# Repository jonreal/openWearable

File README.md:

# openWearable

A real-time hardware/software platform for wearable robotics development based on the BeagleBone platform.

## Overview

openWearable is an open-source project designed to provide a complete hardware and software solution for developing wearable robotic systems, with a focus on real-time control. The platform utilizes the TI BeagleBone Black's Programmable Real-time Units (PRUs) to achieve deterministic high-speed control loops alongside a full Linux environment.

Current/past applications include:
- Upper limb soft exosuits
- Powered ankle-foot prostheses
- Haptic feedback systems
- EMG/IMU sensing and processing

## Getting Started

### Hardware Requirements
- BeagleBone Black or BeagleBone AI64 (see arm64 branch)
- Compatible sensors (see hardware directory)
- Actuators (PAMs, motors, etc.)

### Software Dependencies
- Recommended OS: Debian Linux 12.x (Bookworm) or later
- Kernel: 5.10.168-ti-r72
- PRU Code Generation Tools

### Installation

1. Clone the repository:
   ```
   git clone https://github.com/jonreal/openWearable.git
   cd openWearable
   ```

2. Build the library first:
   ```
   cd library && make
   ```

3. Build an application:
   ```
   cd ../apps/template && make
   ```

4. Run the application:
   ```
   ./bin/template
   ```

### Device Tree Setup

The device tree configures BeagleBone hardware resources for openWearable. Follow these steps:

1. Clone the BeagleBoard-DeviceTrees repository:
   ```
   git clone https://github.com/beagleboard/BeagleBoard-DeviceTrees.git ~/BeagleBoard-DeviceTrees
   ```

2. Create a symbolic link to your device tree file:

   For BeagleBone Black:
   ```
   cd device-tree
   ln -s $PWD/am335x-boneblack-openWearable.dts ~/BeagleBoard-DeviceTrees/src/arm/
   ```

   For BeagleBone Blue:
   ```
   cd device-tree
   ln -s $PWD/am335x-boneblue-openWearable.dts ~/BeagleBoard-DeviceTrees/src/arm/
   ```

3. Compile and install the device tree:
   ```
   cd ~/BeagleBoard-DeviceTrees
   make install_arm
   ```

4. The compiled device tree files will be installed to `/boot/dtbs/<kernel>/`
   (e.g., `/boot/dtbs/5.10.168-ti-r72/`)

5. Edit `/boot/uEnv.txt` to enable the overlay:
   ```
   sudo nano /boot/uEnv.txt
   ```
   
   Add or modify the following line:
   ```
   dtb=am335x-boneblack-openWearable.dtb   # For BeagleBone Black
   # OR
   dtb=am335x-boneblue-openWearable.dtb    # For BeagleBone Blue
   ```

6. Reboot the BeagleBone:
   ```
   sudo reboot
   ```

## Network Setup
To connect to the BeagleBone to Wi-Fi, follow these steps:
   ```
   iwctl

    [iwctl]# station wlan0 scan
    [iwctl]# station wlan0 get-networks
    [iwctl]# station wlan0 connect <SSID>

   ```

## Project Structure

- `apps/` - Application examples and templates
  - `template/` - Starting point for new applications
  - Various application examples (see below)
- `library/` - Core libraries
  - `include/` - Header files
  - `src/` - CPU-side source files
  - `pru_src/` - PRU-specific source files
- `device-tree/` - Hardware configuration
- `hardware/` - PCB designs and hardware documentation
- `gui/` - Visualization tools
- `utils/` - Utility programs
- `scripts/` - Helper scripts

## Application Development

Each application consists of these core files:
- `state.h` - Memory structure definitions
- `format.c` - Logging format definitions
- `cpuloop.c` - Application CPU logic
- `uiloop.c` - User interface logic
- `pruloop.c` - PRU-specific logic

To create a new application, copy the template directory:
```
cd apps
cp -r template my_new_app
cd my_new_app
```

### Build Commands
- First build the library: `cd library && make`
- Then build the app: `cd apps/[app-name] && make`

## Recent Enhancements

1. **Build System Reorganization (March 2025)**
   - Implemented libowpru.a for sharing PRU driver code
   - Each app links against this shared library
   
2. **DMA for Data Transfer (March 2025)**
   - Added DMA support for logging with performance monitoring
   - Use `-d` flag to disable DMA for benchmarking

3. **Binary Logging (In Progress)**
   - Converting text-based logs to binary format
   - Improving performance by reducing formatting overhead

## Example Applications

- **pamtest**: Test pneumatic artificial muscles (PAMs)
- **haptic-tracking**: Haptic feedback control system
- **buttontest**: Simple I/O demonstration
- **imutest**: Test IMU sensors and data processing
- **reflex**: Demonstrate reflex control algorithms

## Publications Using openWearable

### Soft Wearable Robots for Pediatric Movement Disorders
- Realmuto J, Sanger TD. "Assisting Forearm Function in Children With Movement Disorders via A Soft Wearable Robot With Equilibrium-Point Control." Frontiers in Robotics and AI, 2022; 9:877041. doi:10.3389/frobt.2022.877041.
- Repository branch: [equilibrium-point-study](https://github.com/jonreal/openWearable/tree/equilibrium-point-study)

### Powered Ankle-Foot Prostheses
- Realmuto, J. "Towards Personalized Powered Ankle-Foot Prostheses." Dissertation, 2018.
- Repository branch: [poweredAnkle](https://github.com/jonreal/openWearable/tree/poweredAnkle)

### Haptic Feedback for Lower Limb Prostheses
- Sie A, Realmuto J, Rombokas E. "A Lower Limb Prosthesis Haptic Feedback System for Stair Descent." ASME Design of Medical Devices Conference, 2017. doi:10.1115/DMD2017-3409.
- Repository branch: [hapticFeedback](https://github.com/jonreal/openWearable/tree/hapticFeedback)

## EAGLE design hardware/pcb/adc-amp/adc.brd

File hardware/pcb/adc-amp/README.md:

## ADD Details

This folder contains the schematic and component layout for the ADC amplifier circuit using the ADS131M08IPBS chip. The design was created in Autodesk EAGLE and is intended for precision analog signal acquisition.

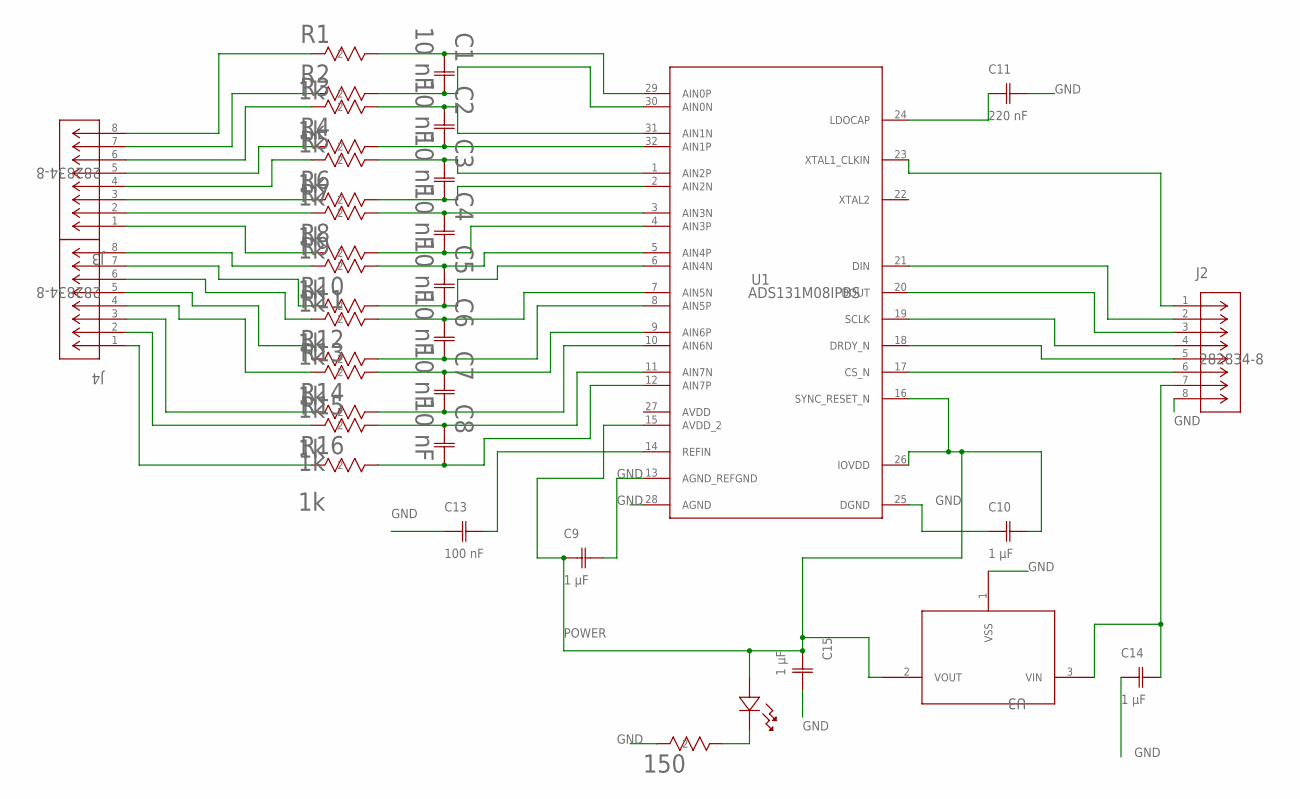
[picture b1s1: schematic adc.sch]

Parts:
C1, C2, C3, C4, C5, C6, C7, C8: 10 nF; CAPC220145_88N_KEM
C9, C10, C14, C15: 1 µF; CAPC220145_140N_KEM
C11: 220 nF; CAPC220145_100N_KEM
C13: 100 nF; CAPC220145_88N_KEM
J2, J3, J4: 282834-8; CONN_282834-8_TEC
LED1: LTST-C190KFKT; LED_LSTS-C190_LTO
R1, R2, R3, R4, R5, R6, R7, R8, R9, R10, R11, R12, R13, R14, R15, R16: 1k; RC0402N_YAG-M
R18: 150; RC0402N_YAG-M
U1: ADS131M08IPBS; PBS0032A_N
U3: XC6206P332MR-GSOT-23_TOR-L; SOT-23_TOR-L

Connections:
AVDD: U1.27 (AVDD)
GND: C9.2, C10.1, C11.2, C13.1, C14.1, C15.2, J2.8, R18.2, U1.13 (AGND_REFGND), U1.25 (DGND), U1.28 (AGND), U3.1 (VSS)
unnamed: C1.1, R1.1, U1.29 (AIN0P)
unnamed: C1.2, R2.1, U1.30 (AIN0N)
unnamed: C2.1, R3.1, U1.31 (AIN1N)
unnamed: C2.2, R4.1, U1.32 (AIN1P)
unnamed: C3.1, R5.1, U1.1 (AIN2P)
unnamed: C3.2, R6.1, U1.2 (AIN2N)
unnamed: C4.1, R7.1, U1.3 (AIN3N)
unnamed: C4.2, R8.1, U1.4 (AIN3P)
unnamed: C5.1, R9.1, U1.5 (AIN4P)
unnamed: C5.2, R10.1, U1.6 (AIN4N)
unnamed: C6.1, R11.1, U1.7 (AIN5N)
unnamed: C6.2, R12.1, U1.8 (AIN5P)
unnamed: C7.1, R13.1, U1.9 (AIN6P)
unnamed: C7.2, R14.1, U1.10 (AIN6N)
unnamed: C8.1, R15.1, U1.11 (AIN7N)
unnamed: C8.2, R16.1, U1.12 (AIN7P)
unnamed: C11.1, U1.24 (LDOCAP)
unnamed: J2.1, U1.23 (XTAL1_CLKIN)
unnamed: J3.8, R1.2
unnamed: J3.7, R2.2
unnamed: J3.6, R3.2
unnamed: J3.5, R4.2
unnamed: J3.4, R5.2
unnamed: J3.3, R6.2
unnamed: J3.2, R7.2
unnamed: J3.1, R8.2
unnamed: J4.8, R9.2
unnamed: J4.7, R10.2
unnamed: J4.6, R11.2
unnamed: J4.5, R12.2
unnamed: J4.4, R13.2
unnamed: J4.3, R14.2
unnamed: J4.2, R15.2
unnamed: J4.1, R16.2
unnamed: J2.4, U1.19 (SCLK)
unnamed: J2.6, U1.17 (CS_N)
unnamed: J2.5, U1.18 (DRDY_N)
unnamed: J2.3, U1.20 (DOUT)
unnamed: J2.2, U1.21 (DIN)
unnamed: C13.2, U1.14 (REFIN)
unnamed: LED1.1 (CATHODE), R18.1
unnamed: C14.2, J2.7, U3.3 (VIN)
POWER: C9.1, C10.2, C15.1, LED1.2 (ANODE), U1.15 (AVDD_2), U1.16 (SYNC_RESET_N), U1.26 (IOVDD), U3.2 (VOUT)

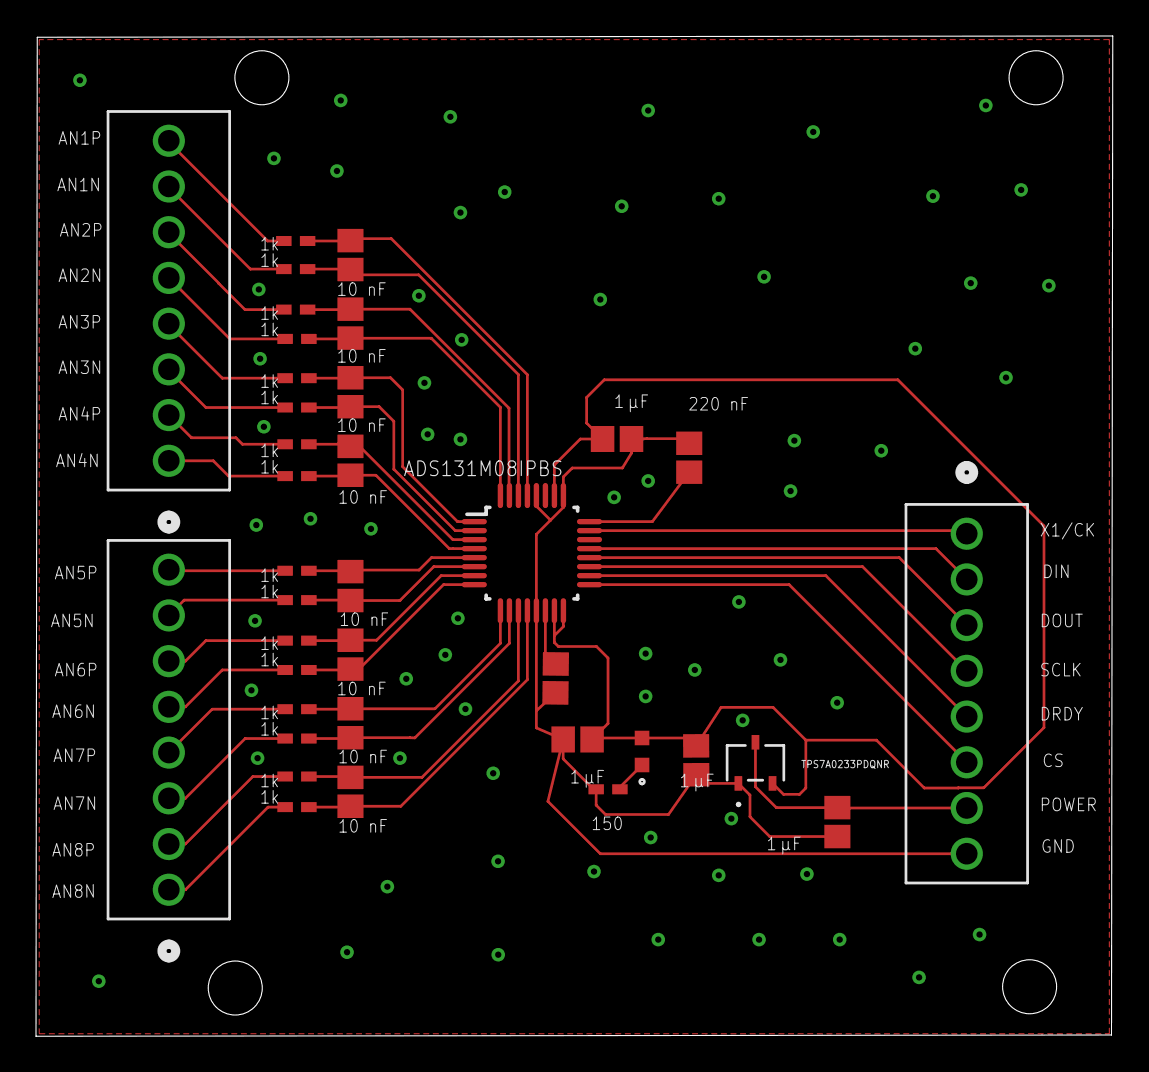
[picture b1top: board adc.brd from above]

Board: 2 copper layers, 59.8 x 55.6 mm, 37 parts (0 on the bottom side), 44 nets.

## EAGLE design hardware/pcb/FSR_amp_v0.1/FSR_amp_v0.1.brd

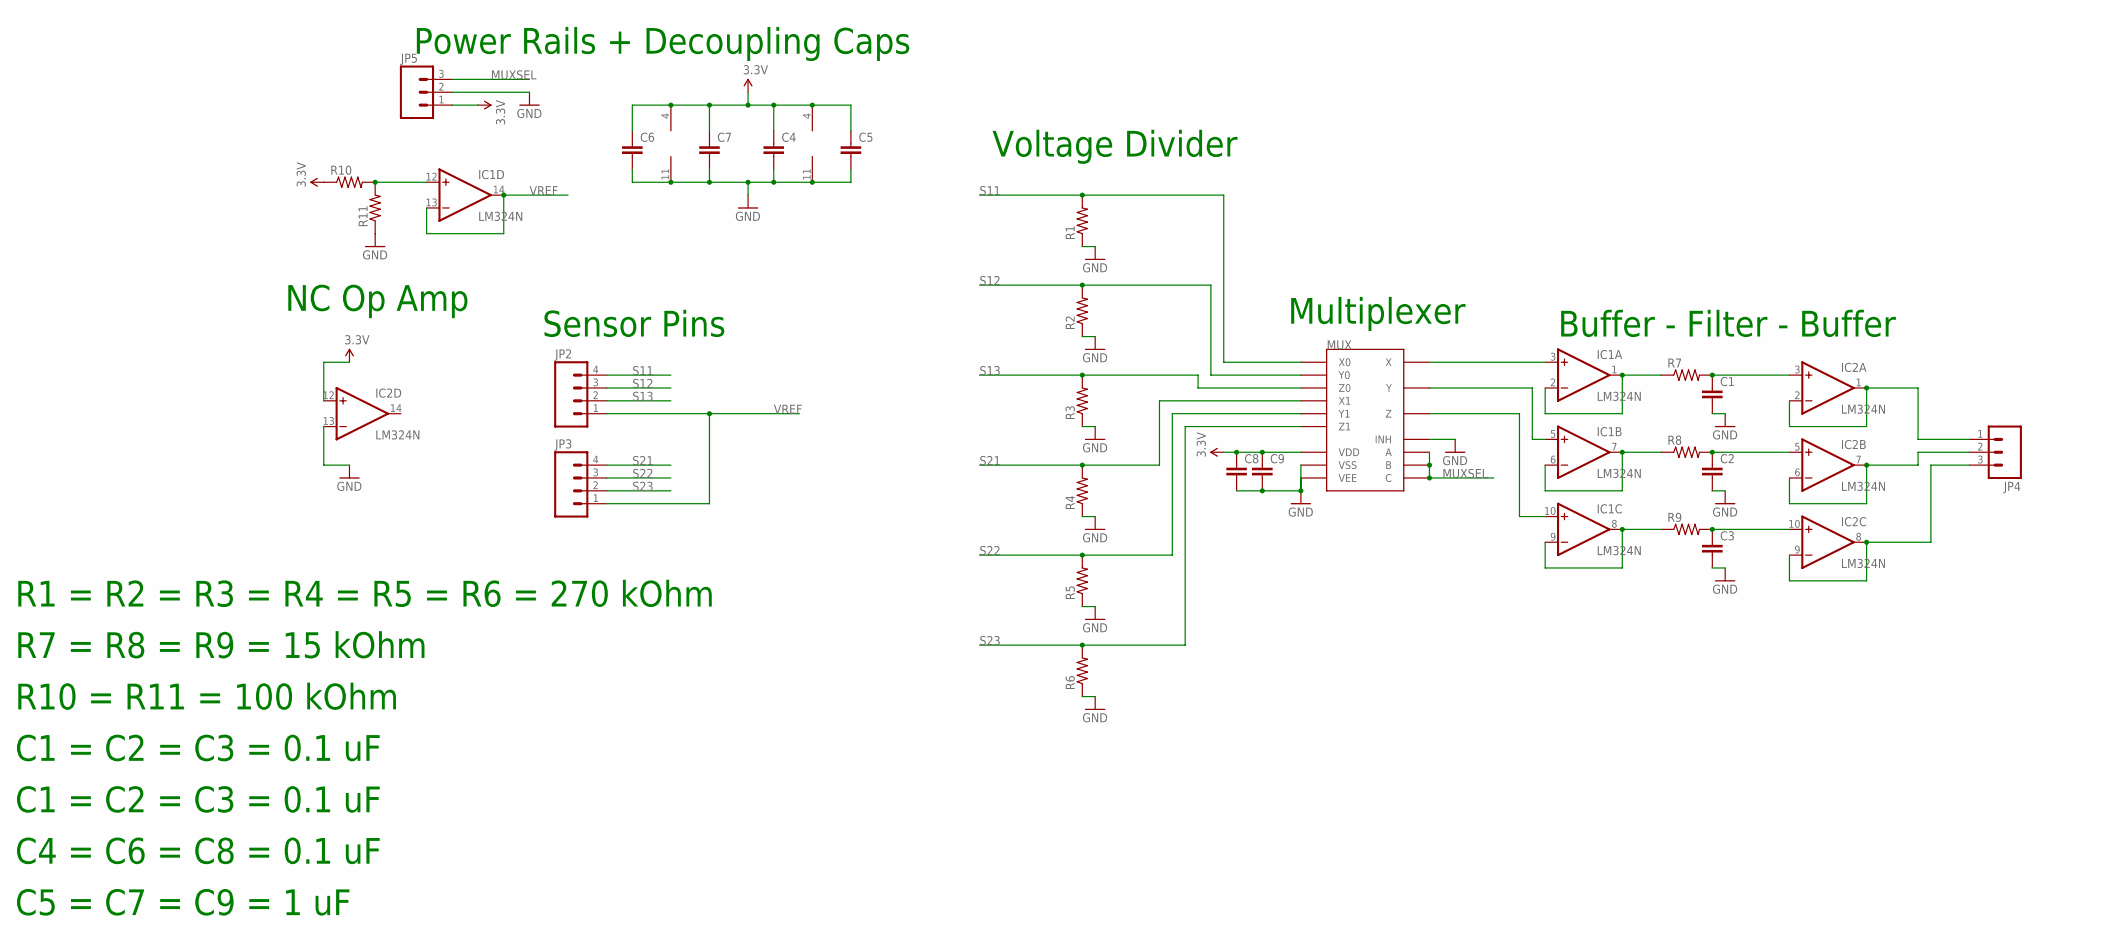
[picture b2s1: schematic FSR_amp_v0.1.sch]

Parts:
C1, C2, C3, C4, C5, C6, C7, C8, C9: CAPPTH; CAP-PTH-SMALL
IC1, IC2: LM324N; DIL14
JP2, JP3: M04POLAR; MOLEX-1X4
JP4, JP5: M03POLAR; MOLEX-1X3
MUX: MC14053BCPDIL16; DIL16
R1, R2, R3, R4, R5, R6, R7, R8, R9, R10, R11: R-US_0207/10; 0207/10

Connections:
3.3V: C4.1, C5.1, C6.1, C7.1, C8.1, C9.1, IC1.4 (V+), IC2.4 (V+), IC2.12 (+IN), JP5.1, MUX.16 (VDD), R10.1
GND: C1.2, C2.2, C3.2, C4.2, C5.2, C6.2, C7.2, C8.2, C9.2, IC1.11 (V-), IC2.11 (V-), IC2.13 (-IN), JP5.2, MUX.6 (INH), MUX.7 (VEE), MUX.8 (VSS), R1.1, R2.1, R3.1, R4.1, R5.1, R6.1, R11.1
MUXSEL: JP5.3, MUX.9 (C), MUX.10 (B), MUX.11 (A)
unnamed: IC1.1 (OUT), IC1.2 (-IN), R7.1
unnamed: IC1.3 (+IN), MUX.14 (X)
unnamed: IC1.6 (-IN), IC1.7 (OUT), R8.1
unnamed: IC1.5 (+IN), MUX.15 (Y)
unnamed: IC1.8 (OUT), IC1.9 (-IN), R9.1
unnamed: IC1.10 (+IN), MUX.4 (Z)
unnamed: IC1.12 (+IN), R10.2, R11.2
unnamed: C1.1, IC2.3 (+IN), R7.2
unnamed: C2.1, IC2.5 (+IN), R8.2
unnamed: C3.1, IC2.10 (+IN), R9.2
unnamed: IC2.8 (OUT), IC2.9 (-IN), JP4.3
unnamed: IC2.6 (-IN), IC2.7 (OUT), JP4.2
unnamed: IC2.1 (OUT), IC2.2 (-IN), JP4.1
S11: JP2.4, MUX.12 (X0), R1.2
S12: JP2.3, MUX.2 (Y0), R2.2
S13: JP2.2, MUX.5 (Z0), R3.2
S21: JP3.4, MUX.13 (X1), R4.2
S22: JP3.3, MUX.1 (Y1), R5.2
S23: JP3.2, MUX.3 (Z1), R6.2
VREF: IC1.13 (-IN), IC1.14 (OUT), JP2.1, JP3.1

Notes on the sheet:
Power Rails + Decoupling Caps
Sensor Pins
Voltage Divider
Multiplexer
Buffer - Filter - Buffer
NC Op Amp
R1 = R2 = R3 = R4 = R5 = R6 = 270 kOhm
R7 = R8 = R9 = 15 kOhm
R10 = R11 = 100 kOhm
C1 = C2 = C3 = 0.1 uF
C4 = C6 = C8 = 0.1 uF
C5 = C7 = C9 = 1 uF

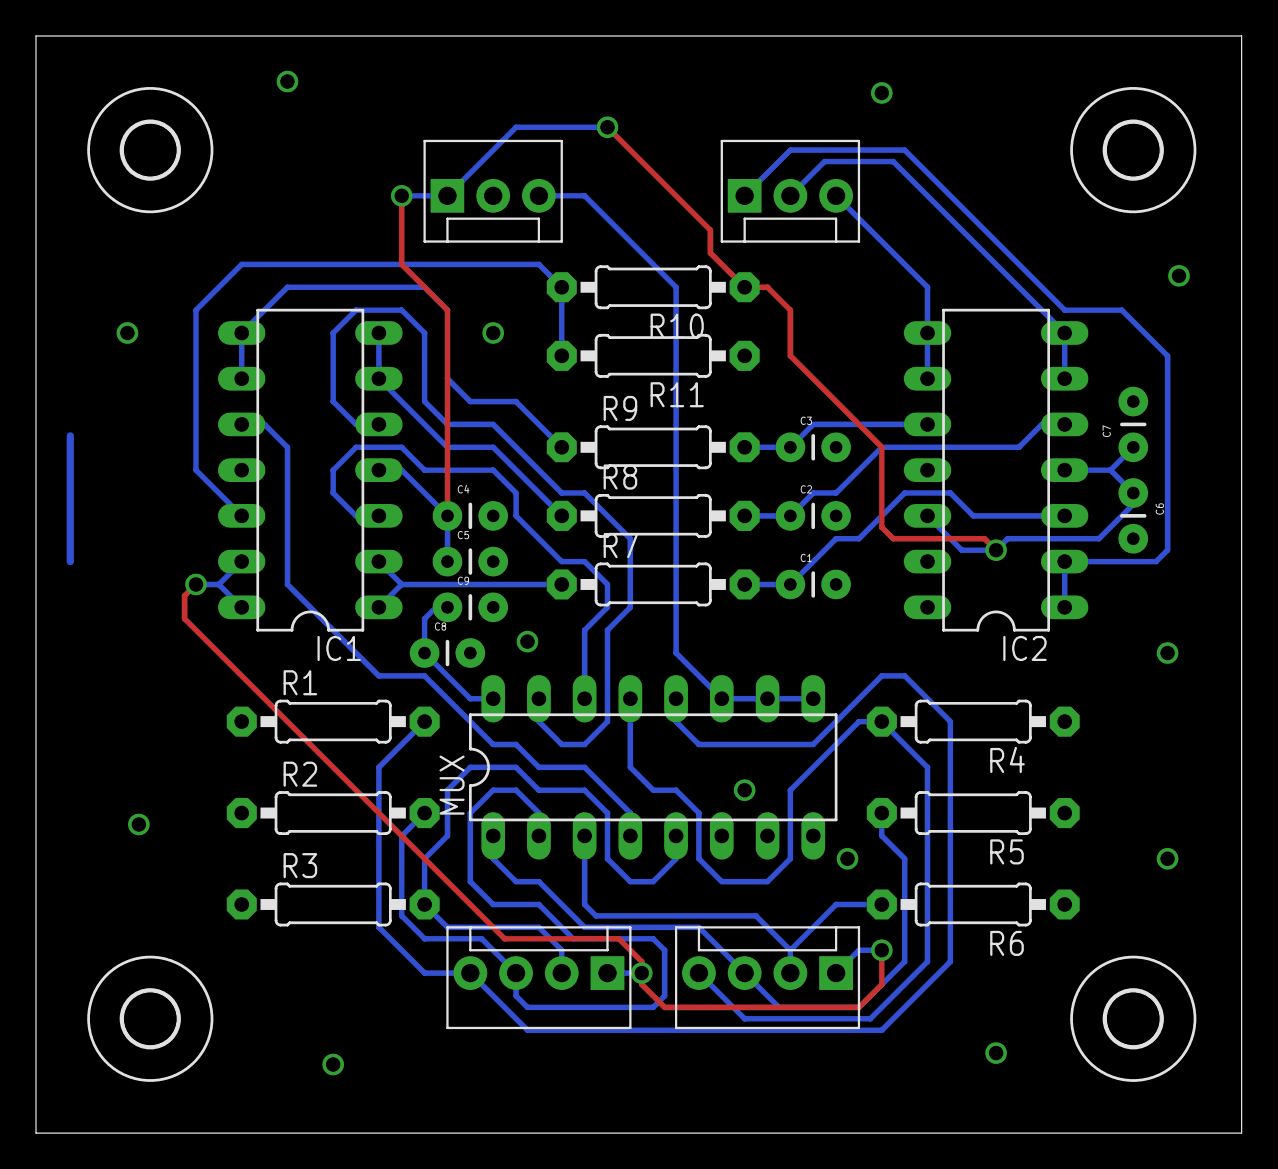
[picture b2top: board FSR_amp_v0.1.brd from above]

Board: 2 copper layers, 67.0 x 61.0 mm, 31 parts (0 on the bottom side), 23 nets.

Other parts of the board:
U$1, U$2, U$3, U$4: 3,0

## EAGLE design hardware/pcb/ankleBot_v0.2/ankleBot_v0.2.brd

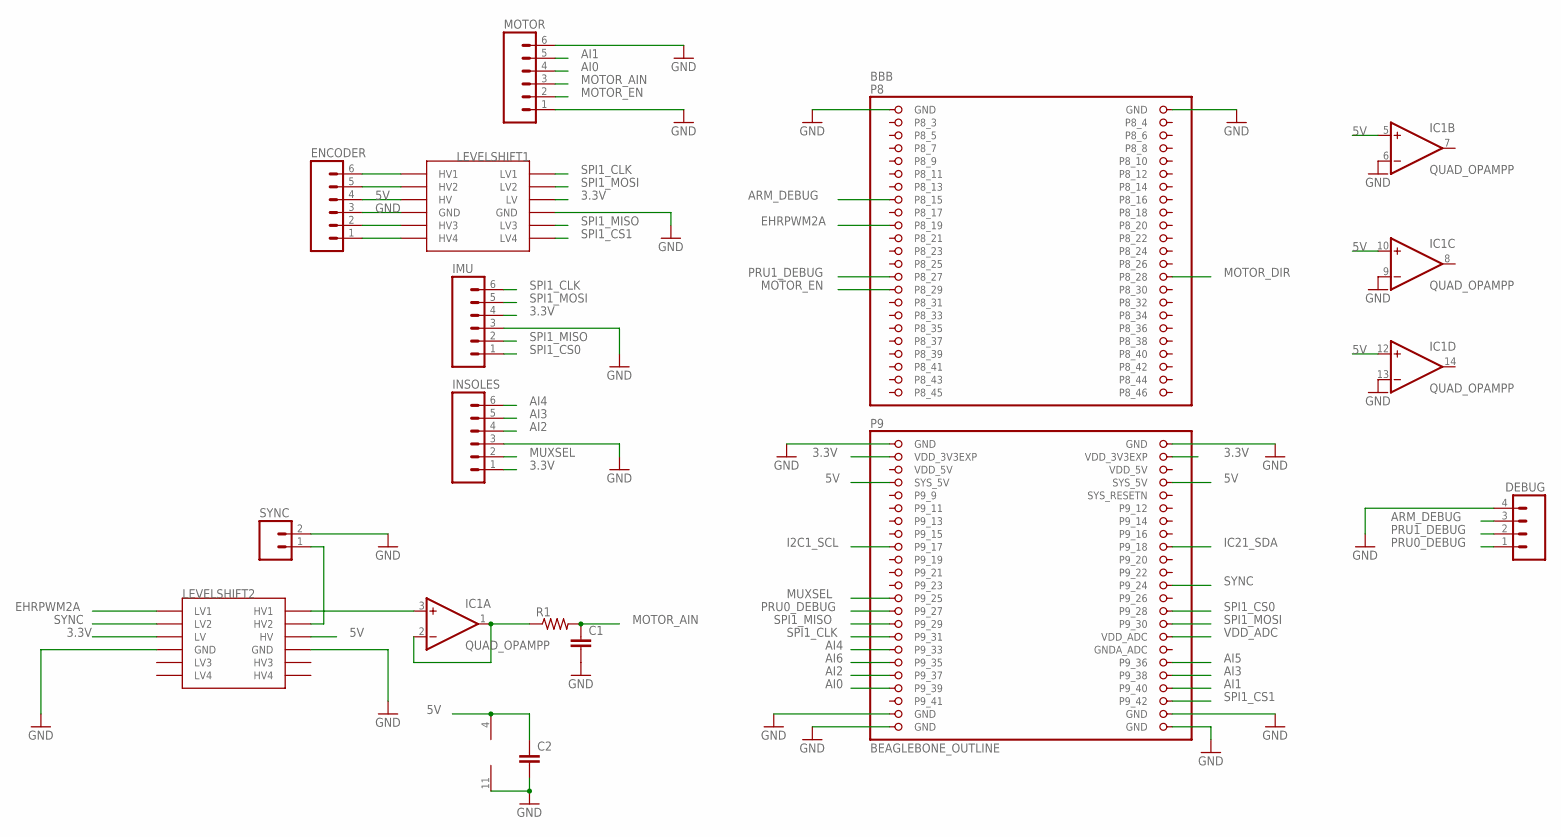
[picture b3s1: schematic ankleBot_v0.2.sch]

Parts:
BBB: BEAGLEBONE_OUTLINE; BEAGLEBONE_SHIELD
C1, C2: C-EU025-025X050; C025-025X050
DEBUG: M04PTH; 1X04
ENCODER: M06POLAR; MOLEX-1X6
IC1: QUAD_OPAMPP; DIL14
IMU: M06POLAR; MOLEX-1X6
INSOLES: M06POLAR; MOLEX-1X6
LEVELSHIFT1, LEVELSHIFT2: SF_LEVEL_CONVERTER; SF_LEVEL_CONVERT
MOTOR: M06POLAR; MOLEX-1X6
R1: R-US_0204/7; 0204/7
SYNC: M02POLAR; MOLEX-1X2

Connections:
3.3V: BBB.49 (VDD_3V3EXP), BBB.50 (VDD_3V3EXP), IMU.4, INSOLES.1, LEVELSHIFT1.P$3 (LV), LEVELSHIFT2.P$3 (LV)
5V: BBB.53 (SYS_5V), BBB.54 (SYS_5V), C2.1, ENCODER.4, IC1.4 (V+), IC1.5 (+IN), IC1.10 (+IN), IC1.12 (+IN), LEVELSHIFT1.P$10 (HV), LEVELSHIFT2.P$10 (HV)
AI0: BBB.85 (P9_39), MOTOR.4
AI1: BBB.86 (P9_40), MOTOR.5
AI2: BBB.83 (P9_37), INSOLES.4
AI3: BBB.84 (P9_38), INSOLES.5
AI4: BBB.79 (P9_33), INSOLES.6
AI5: BBB.82 (P9_36)
AI6: BBB.81 (P9_35)
ARM_DEBUG: BBB.15 (P8_15), DEBUG.3
EHRPWM2A: BBB.19 (P8_19), LEVELSHIFT2.P$1 (LV1)
GND: BBB.1 (GND), BBB.2 (GND), BBB.47 (GND), BBB.48 (GND), BBB.89 (GND), BBB.90 (GND), BBB.91 (GND), BBB.92 (GND), C1.2, C2.2, DEBUG.4, ENCODER.3, IC1.6 (-IN), IC1.9 (-IN), IC1.11 (V-), IC1.13 (-IN), IMU.3, INSOLES.3, LEVELSHIFT1.P$4 (GND), LEVELSHIFT1.P$9 (GND), LEVELSHIFT2.P$4 (GND), LEVELSHIFT2.P$9 (GND), MOTOR.1, MOTOR.6, SYNC.2
I2C1_SCL: BBB.63 (P9_17)
IC21_SDA: BBB.64 (P9_18)
MOTOR_AIN: C1.1, MOTOR.3, R1.2
MOTOR_DIR: BBB.28 (P8_28)
MOTOR_EN: BBB.29 (P8_29), MOTOR.2
MUXSEL: BBB.71 (P9_25), INSOLES.2
unnamed: ENCODER.1, LEVELSHIFT1.P$7 (HV4)
unnamed: IC1.1 (OUT), IC1.2 (-IN), R1.1
unnamed: ENCODER.2, LEVELSHIFT1.P$8 (HV3)
unnamed: LEVELSHIFT2.P$11 (HV2), SYNC.1
unnamed: ENCODER.5, LEVELSHIFT1.P$11 (HV2)
unnamed: ENCODER.6, LEVELSHIFT1.P$12 (HV1)
unnamed: IC1.3 (+IN), LEVELSHIFT2.P$12 (HV1)
PRU0_DEBUG: BBB.73 (P9_27), DEBUG.1
PRU1_DEBUG: BBB.27 (P8_27), DEBUG.2
SPI1_CLK: BBB.77 (P9_31), IMU.6, LEVELSHIFT1.P$1 (LV1)
SPI1_CS0: BBB.74 (P9_28), IMU.1
SPI1_CS1: BBB.88 (P9_42), LEVELSHIFT1.P$6 (LV4)
SPI1_MISO: BBB.75 (P9_29), IMU.2, LEVELSHIFT1.P$5 (LV3)
SPI1_MOSI: BBB.76 (P9_30), IMU.5, LEVELSHIFT1.P$2 (LV2)
SYNC: BBB.70 (P9_24), LEVELSHIFT2.P$2 (LV2)
VDD_5V: BBB.51 (VDD_5V), BBB.52 (VDD_5V)
VDD_ADC: BBB.78 (VDD_ADC)

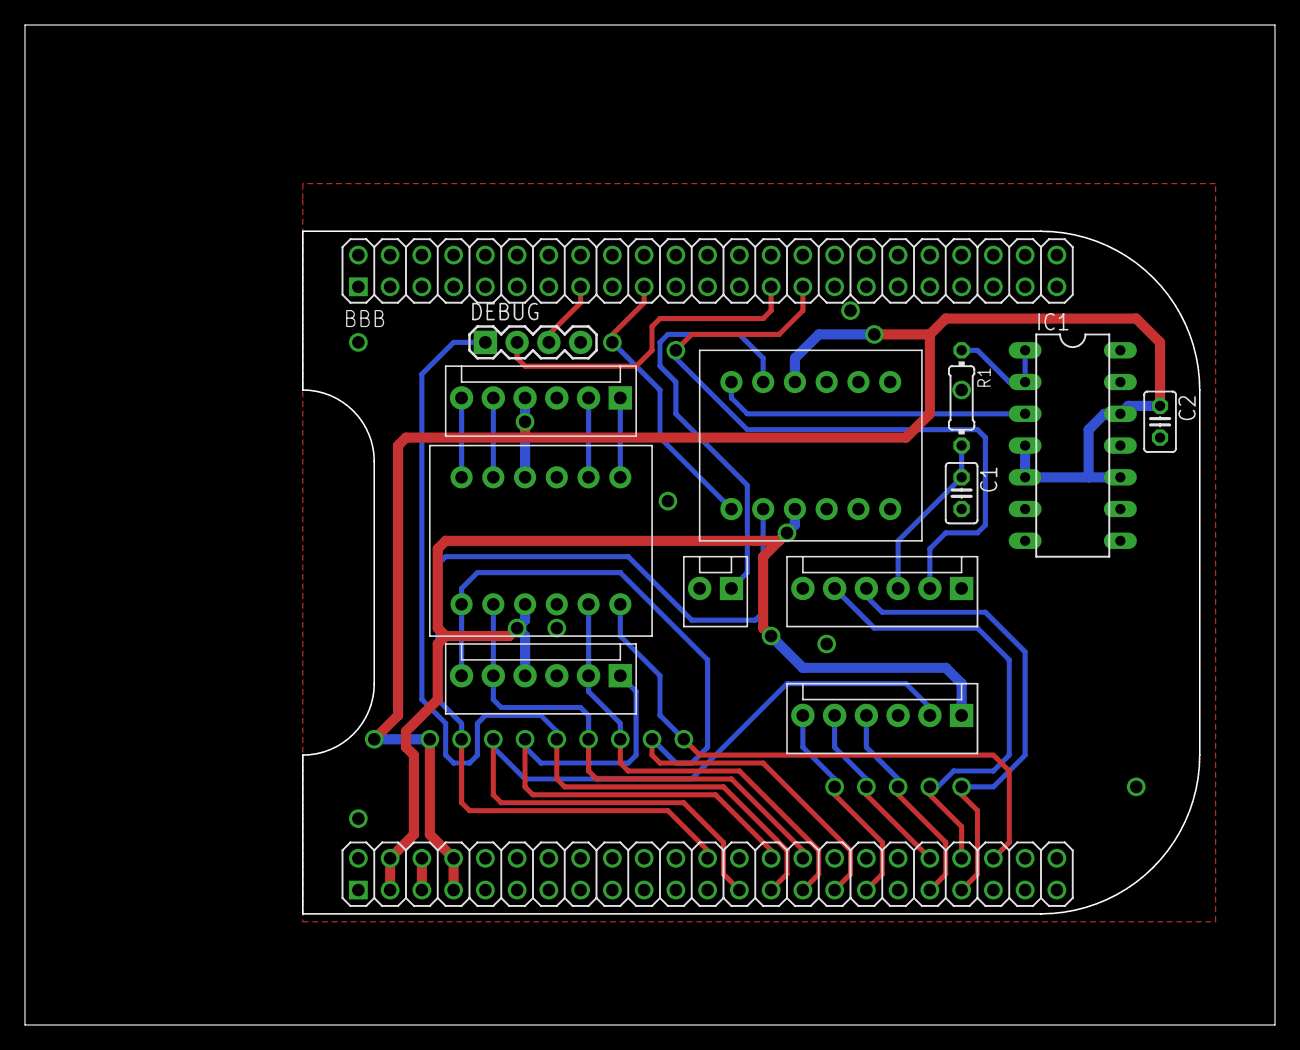
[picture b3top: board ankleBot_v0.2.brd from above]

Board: 2 copper layers, 100.0 x 80.0 mm, 13 parts (0 on the bottom side), 29 nets.

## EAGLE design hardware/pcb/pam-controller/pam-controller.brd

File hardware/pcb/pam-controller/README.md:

This board controls pneumatic valves using a TCA9548A I2C multiplexer and two ULN2803A driver ICs. It supports up to 8 I2C channels and 16 outputs. Logic runs at 3.3V, while VCC supplies power to the valves (e.g., 7V). Use any I2C-capable microcontroller to select channels and drive outputs through the ULN2803A.

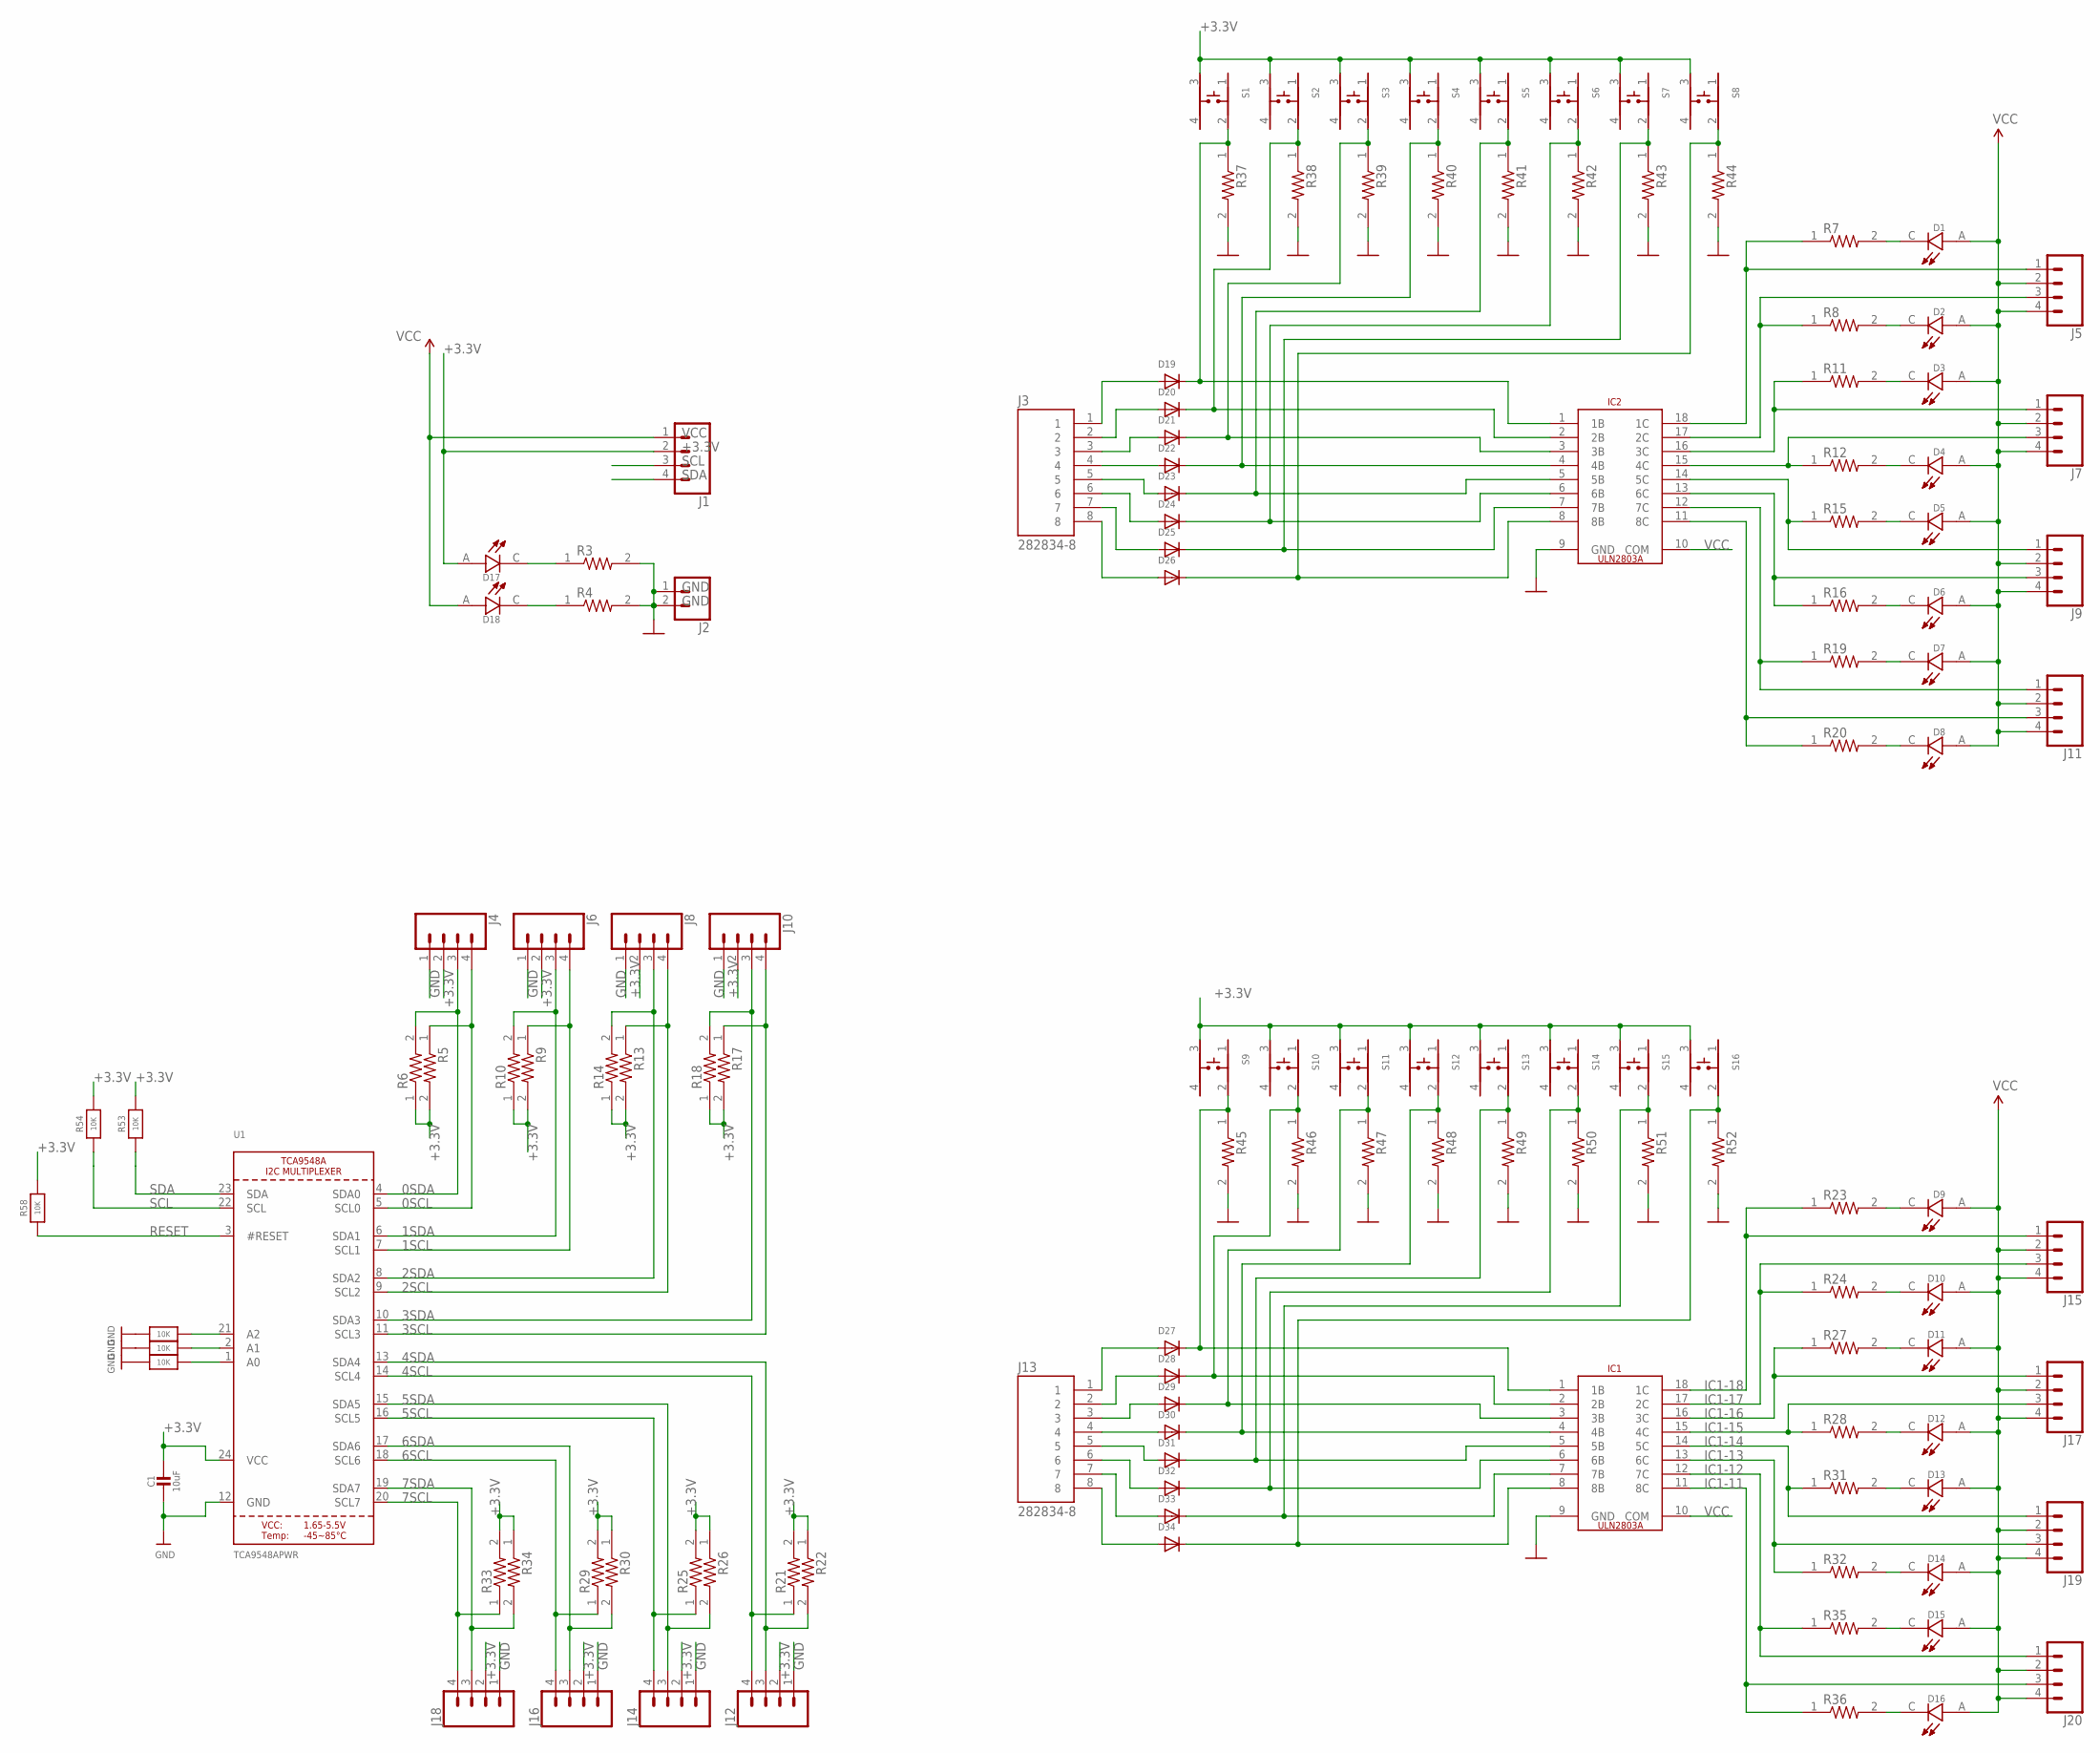
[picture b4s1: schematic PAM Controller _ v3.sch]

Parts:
C1: 10uF; 0805-NO
D1, D2, D3, D4, D5, D6, D7, D8, D9, D10, D11, D12, D13, D14, D15, D16, D17, D18: LTST-C190KGKT; LEDC1608X35N
D19, D20, D21, D22, D23, D24, D25, D26, D27, D28, D29, D30, D31, D32, D33, D34: DIODESOD-523; SOD-523
IC1, IC2: ULN2803A
J1, J4, J5, J6, J7, J8, J9, J10, J11, J12, J14, J15, J16, J17, J18, J19, J20: CONN_04POLAR; MOLEX-1X4
J2: CONN_02POLAR; MOLEX-1X2
J3, J13: 282834-8; TE_282834-8
R3, R4, R5, R6, R7, R8, R9, R10, R11, R12, R13, R14, R15, R16, R17, R18, R19, R20, R21, R22, R23, R24, R25, R26, R27, R28, R29, R30, R31, R32, R33, R34, R35, R36, R37, R38, R39, R40, R41, R42, R43, R44, R45, R46, R47, R48, R49, R50, R51, R52: 1K; RESC1607X60N
R53, R54, R55, R56, R57, R58: 10K; 0805-NO
S1, S2, S3, S4, S5, S6, S7, S8, S9, S10, S11, S12, S13, S14, S15, S16: SKRPACE010; SW_SKRPACE010
U1: TCA9548APWR; TSSOP24

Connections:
0SCL: J4.4, R5.1, U1.5 (SCL0)
0SDA: J4.3, R6.2, U1.4 (SDA0)
1SCL: J6.4, R9.1, U1.7 (SCL1)
1SDA: J6.3, R10.2, U1.6 (SDA1)
2SCL: J8.4, R13.1, U1.9 (SCL2)
2SDA: J8.3, R14.2, U1.8 (SDA2)
3SCL: J10.4, R17.1, U1.11 (SCL3)
3SDA: J10.3, R18.2, U1.10 (SDA3)
4SCL: J12.4, R21.1, U1.14 (SCL4)
4SDA: J12.3, R22.2, U1.13 (SDA4)
5SCL: J14.4, R25.1, U1.16 (SCL5)
5SDA: J14.3, R26.2, U1.15 (SDA5)
6SCL: J16.4, R29.1, U1.18 (SCL6)
6SDA: J16.3, R30.2, U1.17 (SDA6)
7SCL: J18.4, R33.1, U1.20 (SCL7)
7SDA: J18.3, R34.2, U1.19 (SDA7)
+3.3V: C1.1, D17.A, J1.2, J4.2, J6.2, J8.2, J10.2, J12.2, J14.2, J16.2, J18.2, R5.2, R6.1, R9.2, R10.1, R13.2, R14.1, R17.2, R18.1, R21.2, R22.1, R25.2, R26.1, R29.2, R30.1, R33.2, R34.1, R53.2, R54.2, R58.2, S1.3, S2.3, S3.3, S4.3, S5.3, S6.3, S7.3, S8.3, S9.3, S10.3, S11.3, S12.3, S13.3, S14.3, S15.3, S16.3, U1.24 (VCC)
GND: C1.2, IC1.9 (GND), IC2.9 (GND), J2.1, J2.2, J4.1, J6.1, J8.1, J10.1, J12.1, J14.1, J16.1, J18.1, R3.2, R4.2, R37.2, R38.2, R39.2, R40.2, R41.2, R42.2, R43.2, R44.2, R45.2, R46.2, R47.2, R48.2, R49.2, R50.2, R51.2, R52.2, R55.2, R56.2, R57.2, U1.12 (GND)
IC1-11: IC1.11 (8C), J20.3, R36.1
IC1-12: IC1.12 (7C), J20.1, R35.1
IC1-13: IC1.13 (6C), J19.3, R32.1
IC1-14: IC1.14 (5C), J19.1, R31.1
IC1-15: IC1.15 (4C), J17.3, R28.1
IC1-16: IC1.16 (3C), J17.1, R27.1
IC1-17: IC1.17 (2C), J15.3, R24.1
IC1-18: IC1.18 (1C), J15.1, R23.1
IC2-11: IC2.11 (8C), J11.3, R20.1
IC2-12: IC2.12 (7C), J11.1, R19.1
IC2-13: IC2.13 (6C), J9.3, R16.1
IC2-14: IC2.14 (5C), J9.1, R15.1
IC2-15: IC2.15 (4C), J7.3, R12.1
IC2-16: IC2.16 (3C), J7.1, R11.1
IC2-17: IC2.17 (2C), J5.3, R8.1
IC2-18: IC2.18 (1C), J5.1, R7.1
unnamed: D19.K (C), IC2.1 (1B), R37.1, S1.2
unnamed: D19.A, J3.1
unnamed: D20.A, J3.2
unnamed: D21.A, J3.3
unnamed: D22.A, J3.4
unnamed: D23.A, J3.5
unnamed: D24.A, J3.6
unnamed: D25.A, J3.7
unnamed: D27.A, J13.1
unnamed: D27.K (C), IC1.1 (1B), R45.1, S9.2
unnamed: R56.1, U1.2 (A1)
unnamed: R57.1, U1.1 (A0)
unnamed: D28.K (C), IC1.2 (2B), R46.1, S10.2
unnamed: R55.1, U1.21 (A2)
unnamed: D30.A, J13.4
unnamed: D28.A, J13.2
unnamed: D29.A, J13.3
unnamed: D34.A, J13.8
unnamed: D33.A, J13.7
unnamed: D14.C, R32.2
unnamed: D15.C, R35.2
unnamed: D26.A, J3.8
unnamed: D32.A, J13.6
unnamed: D20.K (C), IC2.2 (2B), R38.1, S2.2
unnamed: D21.K (C), IC2.3 (3B), R39.1, S3.2
unnamed: D22.K (C), IC2.4 (4B), R40.1, S4.2
unnamed: D23.K (C), IC2.5 (5B), R41.1, S5.2
unnamed: D24.K (C), IC2.6 (6B), R42.1, S6.2
unnamed: D25.K (C), IC2.7 (7B), R43.1, S7.2
unnamed: D26.K (C), IC2.8 (8B), R44.1, S8.2
unnamed: D29.K (C), IC1.3 (3B), R47.1, S11.2
unnamed: D31.A, J13.5
unnamed: D30.K (C), IC1.4 (4B), R48.1, S12.2
unnamed: D31.K (C), IC1.5 (5B), R49.1, S13.2
unnamed: D32.K (C), IC1.6 (6B), R50.1, S14.2
unnamed: D33.K (C), IC1.7 (7B), R51.1, S15.2
unnamed: D34.K (C), IC1.8 (8B), R52.1, S16.2
unnamed: D16.C, R36.2
unnamed: D12.C, R28.2
unnamed: D13.C, R31.2
unnamed: D11.C, R27.2
unnamed: D10.C, R24.2
unnamed: D9.C, R23.2
unnamed: D8.C, R20.2
unnamed: D7.C, R19.2
unnamed: D6.C, R16.2
unnamed: D1.C, R7.2
unnamed: D17.C, R3.1
unnamed: D18.C, R4.1
unnamed: D5.C, R15.2
unnamed: D4.C, R12.2
unnamed: D3.C, R11.2
unnamed: D2.C, R8.2
RESET: R58.1, U1.3 (#RESET)
SCL: J1.4, R54.1, U1.22 (SCL)
SDA: J1.3, R53.1, U1.23 (SDA)
VCC: D1.A, D2.A, D3.A, D4.A, D5.A, D6.A, D7.A, D8.A, D9.A, D10.A, D11.A, D12.A, D13.A, D14.A, D15.A, D16.A, D18.A, IC1.10 (COM), IC2.10 (COM), J1.1, J5.2, J5.4, J7.2, J7.4, J9.2, J9.4, J11.2, J11.4, J15.2, J15.4, J17.2, J17.4, J19.2, J19.4, J20.2, J20.4

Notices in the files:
device-tree/am335x-boneblue-openWearable.dts:
SPDX-License-Identifier: GPL-2.0-only
Copyright (C) 2012 Texas Instruments Incorporated - https://www.ti.com
parts and their libraries:
SparkFun: Licensing: CC v3.0 Share-Alike You are welcome to use this library for commercial purposes.
COPYRIGHT: Copyright (C) 2025 Ultra Librarian. All rights reserved.
SparkFun-Connectors: Licensing: Creative Commons ShareAlike 4.0 International - https://creativecommons.org/licenses/by-sa/4.0
